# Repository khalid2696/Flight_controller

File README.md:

--------------------------------------------------------------------
Maintained by Khalid M Jaffar and Manoj V from RAFT Lab, IIT Madras
--------------------------------------------------------------------

Code repository for embedded flight controller board based on STM32 microcontroller. Its functionalities are
1. Sensor interfacing - MPU9250, MS5611 and PX4FLOW
2. Controller         - PID, PI-PID, Backstepping, etc.
3. Datalogging

Note to contributors: 
1. Add Readme.md file to the folders that you push
2. Commit codes and make sure it is self-explanatory
3. Fork the repository if you are making iterations
4. Refrain from directly modifying the files of master folder
5. Include adequate comments in the scripts

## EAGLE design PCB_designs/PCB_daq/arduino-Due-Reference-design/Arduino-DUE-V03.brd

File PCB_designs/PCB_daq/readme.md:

I planned to use Arduino Due to build this FCB.
Plan was later dumped. Preference was given to STM32 based board

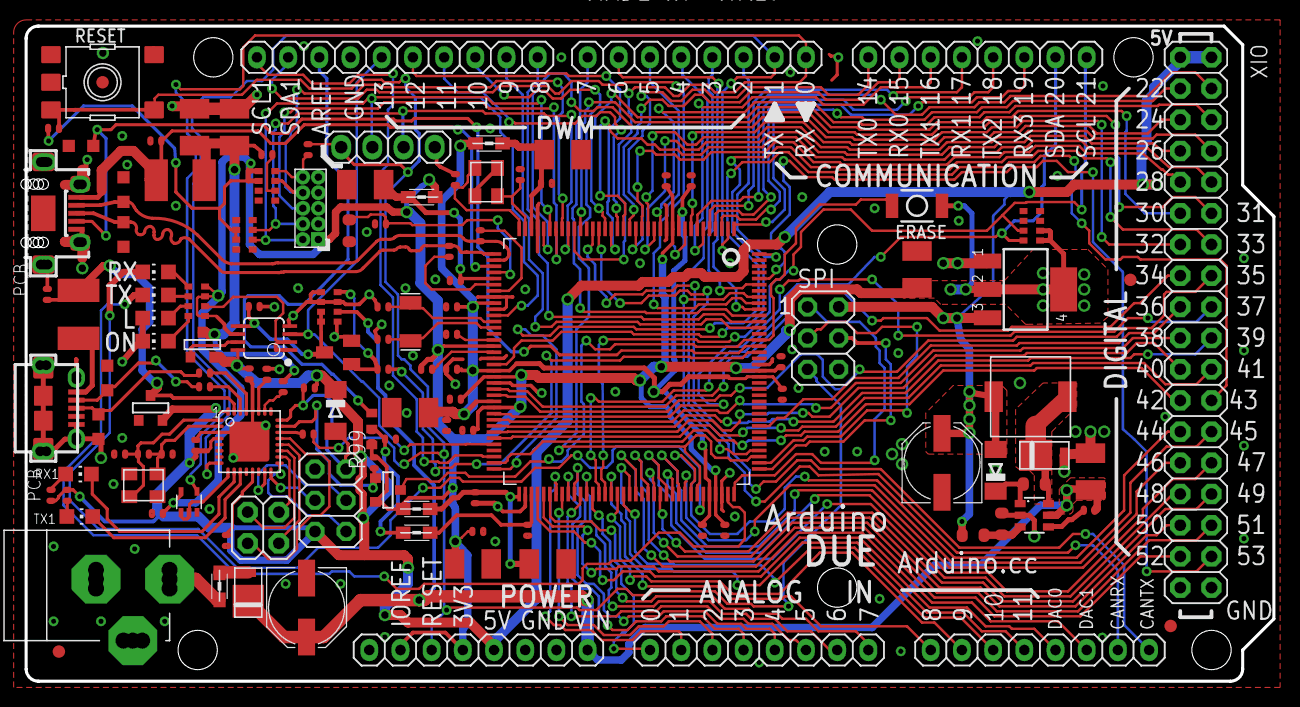
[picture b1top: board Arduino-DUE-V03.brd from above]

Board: 2 copper layers, 101.6 x 53.3 mm, 129 parts (0 on the bottom side), 150 nets.

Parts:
ADCH: 8x1F-H8.5; 1X08
ADCL: 8x1F-H8.5; 1X08
BR1: NM; J0402
C1, C2, C3, C11, C27, C29, C33, C35, C41: 10u; SMC_B
C4, C5, C6, C7, C8, C9, C10, C12, C13, C14, C15, C16, C17, C18, C19, C28, C30, C31, C32, C34, C36, C37: 100n; C0402
C20, C26: 10n; C0402
C21, C22, C25, C39, C40: 22p; C0402
C23, C24: 22pF_NM; C0402
C38: 1u; C0402
C42: 10n; C0603-ROUND
COMMUNICATION: 8x1F-H8.5; 1X08
D2, D3: CD1206-S01575; MINIMELF
D4, D5: SS1P3L; DO220AAL
DEBUG: STRIP 4x1V M; 1X04
ERASE: SMD_157SW
F1, F2: MF-MSMF050-2 500mA; L1812
FID1, FID2, FID3, FID4: FIDUCIALMOUNT; FIDUCIA-MOUNT
IC1: LMV358IDGKR; MSOP08
IC2: LM2734Y; SOT23-6
IC4: NCP1117ST33T3G -3V3; SOT223
IC6: ATMEGA16U2-MU; MLF32
IC10: 74LVC1G125DCK; SC70-5
ICSP1: 3x2M; 2X03
J3: USB-MICRO B; CON2_USB_MICRO_B_AT
JP5: 2x2M - NM; 2X02
JR1: 0R; R0402
JTAG: PINHEAD_2X05_127
L: YELLOW; CHIP-LED0805
L1, L2, L3, L5, L6: MH2029-300Y; 0805
L4: 10u SRR0604-100ML; SRR0604
ON: GREEN; CHIP-LED0805
PC1, PC2: 47u; PANASONIC_D
POWER: 8x1F-H8.5; 1X08
PWMH: 10x1F-H8.5; 1X10
PWML: 8x1F-H8.5; 1X08
Q2: BC847BSMD; SOT23
R1: 0R; R0402
R2, R13, R18, R99: 10K; R0402
R3, R14, R15, R21, R23: 1K; R0402
R4: 100K; R0402
R5, R6: 39R 1%; R0402
R7: 6k8 1%; R0603-ROUND
R8: 0R_NM; R0402
R9: 1M_NM; R0402
R10: 10k; R0402
R11: 10K; R0603-ROUND
R12: 52K3; R0603-ROUND
R19, R20: 22R; R0402
RESET: TS42
RN1, RN2, RN4: 100K; CAT16
RN3: 1k; CAY16
RN5: 1K5; CAT16
RX, RX1: YELLOW; CHIP-LED0805
SPI: 3x2M; 2X03
T1, T2, T3: FDN340P; SOT-23
TX, TX1: YELLOW; CHIP-LED0805
U1: ATSAM3X8EA-AU; LQFP144
USB1: MICRO-USB-AB1; MCR-AB1-S-RA-SMT
X2: POWERSUPPLY_DC21MMX; POWERSUPPLY_DC-21MM
XIO: 18x2F-H8.5; 2X18
Y1: 12MHz KX-7 20pF; CRYSTAL-3.2-2.5
Y2: 32.768Khz; RESONATOR_EPSON_FC_145
Y4: 16MHz KX-7 20pF; CRYSTAL-3.2-2.5
Z1, Z2, Z3, Z4, Z5: CG0603MLC-05E; CT/CN0603

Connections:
8PB4: IC6.18, JP5.1
8PB5: IC6.19, JP5.3
8PB6: IC6.20, JP5.2
8PB7: IC6.21, JP5.4
16U2-TX: IC6.9, IC10.1, IC10.2
+3V3: BR1.3, C1.+, C4.2, C5.2, C6.2, C7.2, C8.2, C18.2, C20.2, C29.+, C37.1, ERASE.1, IC1.6, IC4.2, IC4.4, IC10.5, JR1.1, JTAG.1, L1.1, L2.1, POWER.2, POWER.4, R4.2, R99.2, RN1.5, RN1.6, RN2.2, RN2.3, RN3.5, RN3.7, RN3.8, RN5.1, RN5.2, T3.2, U1.11, U1.52, U1.57, U1.62, U1.105, U1.125
+5V: C30.2, C36.1, D2.C, D3.A, IC1.8, IC4.3, IC6.4, IC6.32, ICSP1.2, L4.P$2, PC2.+, POWER.5, R12.1, R13.2, R14.1, R15.1, SPI.2, T1.2, T2.2, XIO.1, XIO.2
AD0: ADCL.1, U1.78
AD1: ADCL.2, U1.79
AD2: ADCL.3, U1.80
AD3: ADCL.4, U1.81
AD4: ADCL.5, U1.82
AD5: ADCL.6, U1.83
AD6: ADCL.7, U1.84
AD7: ADCL.8, U1.85
AD8: ADCH.1, U1.88
AD9: ADCH.2, U1.89
AD10: ADCH.3, U1.90
AD11(TXD3): ADCH.4, U1.91
AD14(RXD3): U1.92, XIO.33
AREF: BR1.1, PWMH.8
AVREF: C19.2, L3.2, U1.75
AVREFL: BR1.2, C34.2, JR1.2, L3.1
BD+: J3.P3, R20.2, Z4.2
BD-: J3.P2, R19.2, Z3.2
BOOST: C42.1, D3.C, IC2.1
CANRX0: ADCH.7, U1.24
CANTX0: ADCH.8, U1.23
CANTX1/IO: U1.140, XIO.34
CMP: C31.2, IC1.5, Q2.3, RN4.3, RN4.4
D+: R6.1, U1.37, USB1.3, Z1.1
D-: R5.1, U1.38, USB1.2, Z2.1
DAC0(CANRX1): ADCH.5, U1.76
DAC1: ADCH.6, U1.77
DTR: IC6.13, R18.1
EN: IC2.4, R10.2
ERASE_CMD: IC6.23, R99.1, T3.3
ERASE_S: ERASE.2, T3.1, U1.130
FB: IC2.3, R11.1, R12.2
GATE_CMD: IC1.7, T1.3
GND: C1.-, C2.-, C3.-, C4.1, C5.1, C6.1, C7.1, C8.1, C9.1, C10.1, C11.-, C12.1, C13.1, C14.1, C15.1, C16.1, C17.1, C18.1, C19.1, C21.2, C22.2, C23.2, C24.2, C25.2, C26.2, C27.-, C28.2, C29.-, C30.1, C31.1, C32.1, C33.-, C34.1, C35.-, C36.2, C37.2, C38.2, C39.2, C40.2, C41.-, D4.P$2, DEBUG.1, IC1.4, IC2.2, IC4.1, IC6.3, IC6.28, IC6.33, IC10.3, ICSP1.6, J3.P5, J3.P$1, J3.P$2, J3.P$3, J3.P$4, J3.P$5, J3.P$6, J3.P$7, J3.P$8, J3.S1, J3.S2, J3.S3, J3.S4, J3.S5, J3.S6, JTAG.3, JTAG.5, JTAG.9, L.C, ON.C, PC1.-, PC2.-, POWER.6, POWER.7, PWMH.7, Q2.2, R2.1, R7.1, R8.1, R11.2, R18.2, RESET.1, RESET.2, RN1.1, RN1.2, RN1.7, RN1.8, RN2.1, RN2.4, RN2.5, RN2.8, RN4.1, RN4.2, RN4.5, RN4.7, SPI.6, T2.3, U1.12, U1.33, U1.44, U1.46, U1.54, U1.58, U1.74, U1.106, U1.126, USB1.5, USB1.P$1, USB1.P$2, USB1.P$3, USB1.P$4, USB1.P$5, USB1.P$6, USB1.P$7, USB1.P$8, USB1.P$9, USB1.P$10, USB1.P$11, USB1.S1, USB1.S2, USB1.S3, USB1.S4, X2.1, X2.3, XIO.35, XIO.36, Y1.2, Y1.4, Y4.2, Y4.4, Z1.2, Z2.2, Z3.1, Z4.1, Z5.1
JTAG_RESET: JTAG.10, R1.1, RN1.4
JTAG_TCK: DEBUG.2, JTAG.4, RN2.7, U1.28
JTAG_TDI: JTAG.8, RN1.3, U1.29
JTAG_TDO: JTAG.6, U1.30
JTAG_TMS: DEBUG.3, JTAG.2, RN2.6, U1.31
L13: IC1.1, IC1.2, RN3.6
MASTER-RESET: C20.1, DEBUG.4, POWER.3, R1.2, R23.2, RESET.3, RESET.4, SPI.5, U1.47
MISO: SPI.1, U1.108
MISO2: IC6.17, ICSP1.1
MOSI: SPI.4, U1.109
MOSI2: IC6.16, ICSP1.4
unnamed: IC6.26, R21.1
unnamed: L.A, RN3.3
unnamed: ON.A, RN3.4
unnamed: R15.2, RX1.A
unnamed: R8.2, U1.51
unnamed: Q2.1, R3.2, RN4.8
unnamed: R4.1, U1.53
unnamed: D5.P$2, L6.1
unnamed: R5.2, U1.43
unnamed: R6.2, U1.42
unnamed: R14.2, TX1.A
unnamed: RN3.1, RX.A
unnamed: RN3.2, TX.A
PIN22: U1.1, XIO.3
PIN23: U1.7, XIO.4
PIN24: U1.8, XIO.5
PIN25: U1.13, XIO.6
PIN26: U1.14, XIO.7
PIN27: U1.15, XIO.8
PIN28: U1.16, XIO.9
PIN29: U1.19, XIO.10
PIN30: U1.22, XIO.11
PIN31: U1.26, XIO.12
PIN32: U1.32, XIO.13
PIN33: U1.55, XIO.14
PIN34: U1.59, XIO.15
PIN35: U1.60, XIO.16
PIN36: U1.116, XIO.17
PIN37: U1.63, XIO.18
PIN38: U1.64, XIO.19
PIN39: U1.65, XIO.20
PIN40: U1.66, XIO.21
PIN41: U1.67, XIO.22
PIN42: U1.71, XIO.23
PIN43: U1.72, XIO.24
PIN44: U1.101, XIO.25
PIN45: U1.100, XIO.26
PIN46: U1.99, XIO.27
PIN47: U1.98, XIO.28
PIN48: U1.97, XIO.29
PIN49: U1.96, XIO.30
PIN50: U1.95, XIO.31
PIN51: U1.94, XIO.32
PWM2: PWML.3, U1.144
PWM3: PWML.4, U1.139
PWM5: PWML.6, U1.136
PWM6: PWML.7, U1.135
PWM7: PWML.8, U1.134
PWM8: PWMH.1, U1.133
PWM9: PWMH.2, U1.132
PWM11: PWMH.4, U1.20
PWM12: PWMH.5, U1.21
PWM13: IC1.3, PWMH.6, U1.68
RD+: IC6.29, R20.1
RD-: IC6.30, R19.1
RESET2: D2.A, IC6.24, ICSP1.5, R13.1
RESET_CMD: IC6.22, R23.1
RX: IC10.4, PWML.1, U1.27
RXD0: COMMUNICATION.2, U1.18
RXD1: COMMUNICATION.4, U1.5
RXD2: COMMUNICATION.6, U1.3
RXL: RX.C, U1.103
RXL-U2: IC6.10, RX1.C
SCK2: IC6.15, ICSP1.3
SCL0-3: COMMUNICATION.8, RN5.7, U1.87
SCL1: PWMH.10, U1.70
SDA0-3: COMMUNICATION.7, RN5.8, U1.86
SDA1: PWMH.9, U1.9
SPCK: SPI.3, U1.110
SS0/PWM10: PWMH.3, U1.102, U1.111
SS1/PWM4: PWML.5, U1.112, U1.137
SW: C42.2, D4.P$1, IC2.6, L4.P$1
TX: IC6.8, PWML.2, U1.2
TXD0: COMMUNICATION.1, U1.17
TXD1: COMMUNICATION.3, U1.6
TXD2: COMMUNICATION.5, U1.4
TXL: TX.C, U1.107
TXL-U2: IC6.11, TX1.C
UOTGID: U1.129, USB1.4, Z5.2
UOTGVBOF: R3.1, U1.128
USBVCC: C27.+, C35.+, F1.1, R2.2, R21.2, T1.1
USBVCCU2: C28.1, F2.1, IC6.31, T2.1
VBG: C25.1, R7.2, U1.40
VDDANA: C3.+, C10.2, L1.2, U1.73
VDDOUT: C11.+, C12.2, C13.2, C14.2, C15.2, C16.2, C17.2, L5.1, U1.10, U1.45, U1.56, U1.61, U1.104, U1.124
VDDOUTMI: C2.+, C9.2, L2.2, U1.41
VDDPLL: C32.2, C33.+, L5.2, U1.34
VIN: C41.+, D5.P$1, IC2.5, PC1.+, POWER.8, R10.1, RN4.6
VIN+: L6.2, X2.2
VUCAP: C38.1, IC6.27
XIN: C22.1, U1.36, Y1.1
XIN32: C24.1, U1.48, Y2.P$2
XOUT: C21.1, U1.35, Y1.3
XOUT32: C23.1, U1.49, Y2.P$1
XT1: C39.1, IC6.1, R9.1, Y4.1
XT2: C40.1, IC6.2, R9.2, Y4.3
XUSB: C26.1, F1.2, U1.39, USB1.1
XVCC: F2.2, J3.P1

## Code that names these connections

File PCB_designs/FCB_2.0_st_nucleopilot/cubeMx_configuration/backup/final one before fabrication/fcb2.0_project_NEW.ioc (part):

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Mcu.Name=STM32F401R(D-E)Tx
Mcu.Package=LQFP64
Mcu.UserName=STM32F401RETx
PA0-WKUP.Mode=CTS_RTS
PA0-WKUP.Signal=USART2_CTS
PA1.Mode=CTS_RTS
PA1.Signal=USART2_RTS
PA10.Mode=Asynchronous
PA10.Signal=USART1_RX
PA11.Mode=CTS_RTS
PA11.Signal=USART1_CTS
PA12.Mode=CTS_RTS
PA12.Signal=USART1_RTS
PA13.Mode=JTAG_4_pins
PA13.Signal=SYS_JTMS-SWDIO
PA14.Mode=JTAG_4_pins
PA14.Signal=SYS_JTCK-SWCLK
PA15.Mode=JTAG_4_pins
PA15.Signal=SYS_JTDI
PA2.Mode=Asynchronous
PA2.Signal=USART2_TX
PA3.Mode=Asynchronous
PA3.Signal=USART2_RX
PA5.GPIOParameters=GPIO_Label
PA5.GPIO_Label=USER LED_nuleo
PA5.Signal=GPIO_Output
PA6.Signal=ADCx_IN6
PA7.Signal=ADCx_IN7
PA8.Mode=I2C
PA8.Signal=I2C3_SCL
PA9.Mode=Asynchronous
PA9.Signal=USART1_TX
PB0.Signal=S_TIM3_CH3
PB1.Signal=S_TIM3_CH4
PB10.Mode=Full_Duplex_Master
PB10.Signal=SPI2_SCK
PB12.Mode=NSS_Signal_Hard_Output
PB12.Signal=SPI2_NSS
PB13.GPIOParameters=GPIO_Label
PB13.GPIO_Label=triColor LED
PB13.Signal=GPIO_Output
PB14.GPIOParameters=GPIO_Label
PB14.GPIO_Label=triColor LED
PB14.Signal=GPIO_Output
PB15.GPIOParameters=GPIO_Label
PB15.GPIO_Label=triColor LED
PB15.Signal=GPIO_Output
PB3.Mode=JTAG_4_pins
PB3.Signal=SYS_JTDO-SWO
PB4.Signal=S_TIM3_CH1
PB5.Signal=S_TIM3_CH2
PB6.Signal=S_TIM4_CH1
PB7.Signal=S_TIM4_CH2
PB8.Signal=S_TIM4_CH3
PB9.Signal=S_TIM4_CH4
PC10.GPIOParameters=GPIO_Label
PC10.GPIO_Label=extI10_imu
PC10.Signal=GPXTI10
PC13-ANTI_TAMP.GPIOParameters=GPIO_Label
PC13-ANTI_TAMP.GPIO_Label=USER_BUTTON_BLUE_nucleo
PC13-ANTI_TAMP.Signal=GPIO_Input
PC14-OSC32_IN.Mode=LSE-External-Oscillator
PC14-OSC32_IN.Signal=RCC_OSC32_IN
PC15-OSC32_OUT.Mode=LSE-External-Oscillator
PC15-OSC32_OUT.Signal=RCC_OSC32_OUT
PC2.Mode=Full_Duplex_Master
PC2.Signal=SPI2_MISO
PC3.Mode=Full_Duplex_Master
PC3.Signal=SPI2_MOSI
PC4.GPIOParameters=GPIO_Label
PC4.GPIO_Label=EXT14_RX_PPM
PC4.Signal=GPXTI4
PC6.Mode=Synchronous
PC6.Signal=USART6_TX
PC7.Mode=Synchronous
PC7.Signal=USART6_RX
PC8.Mode=Synchronous
PC8.Signal=USART6_CK
PC9.Mode=I2C
PC9.Signal=I2C3_SDA
PH0\ -\ OSC_IN.Mode=HSE-External-Oscillator
PH0\ -\ OSC_IN.Signal=RCC_OSC_IN
PH1\ -\ OSC_OUT.Mode=HSE-External-Oscillator
PH1\ -\ OSC_OUT.Signal=RCC_OSC_OUT
RCC.HSE_VALUE=25000000
RCC.SYSCLKFreq_VALUE=16000000

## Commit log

2017-09-25 Readme File
2017-09-25 comment
2017-09-25 landf
2017-09-25 the final one
2017-09-26 Delete LICENSE
    Removed GPL license: more liberal license needed
2025-05-02 added files
